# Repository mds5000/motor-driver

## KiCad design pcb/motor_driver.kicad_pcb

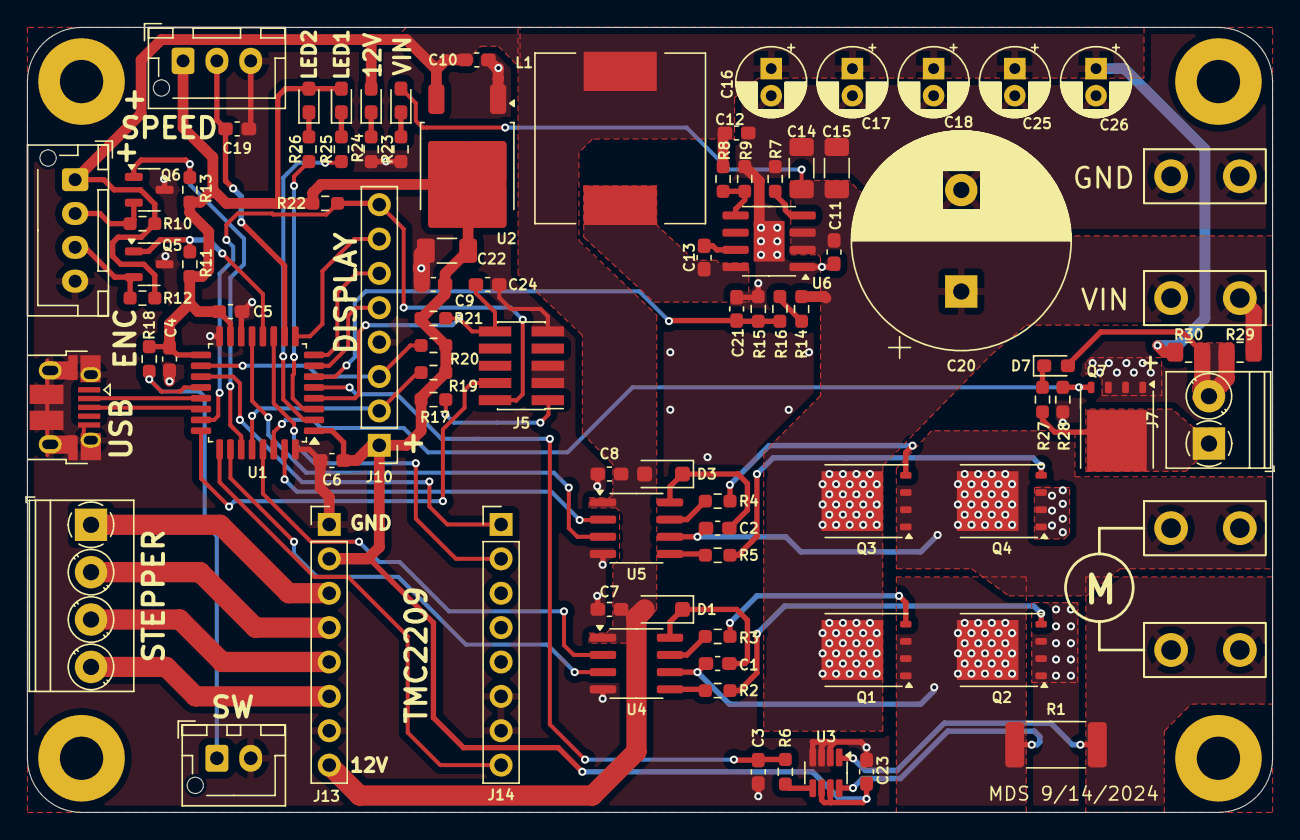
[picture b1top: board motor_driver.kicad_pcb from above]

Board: 2 copper layers, 92.0 x 58.0 mm, 95 parts (0 on the bottom side), 63 nets.

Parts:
C1, C2, C3, C4, C5, C6, C7, C8, C9, C10, C11, C12, C13, C19, C21, C23, C24: 0.1uF; C_0603_1608Metric_Pad1.08x0.95mm_HandSolder
C14, C15: 1uF; C_1206_3216Metric_Pad1.33x1.80mm_HandSolder
C16, C17, C18, C25, C26: 10uF; CP_Radial_D5.0mm_P2.00mm
C20: 470uF; CP_Radial_D16.0mm_P7.50mm
C22: 4.7uF; C_1206_3216Metric_Pad1.33x1.80mm_HandSolder
D1, D3: 1N5819WS; D_SOD-123F
D2, D4, D5, D6, D7: LED; LED_0603_1608Metric_Pad1.05x0.95mm_HandSolder
H1, H2, H3, H4: MountingHole; MountingHole_3.2mm_M3_Pad
J1, J2, J3, J4: 1217861-1; CONN_QuickTab_TE_Conn_1217861-1
J5: Conn_ARM_JTAG_SWD_10; PinHeader_2x05_P1.27mm_Vertical_SMD
J6: Screw_Terminal_01x04; TerminalBlock_Phoenix_PT-1,5-4-3.5-H_1x04_P3.50mm_Horizontal
J7: Screw_Terminal_01x02; TerminalBlock_Phoenix_PT-1,5-2-3.5-H_1x02_P3.50mm_Horizontal
J8: Conn_01x03; JST_XH_B3B-XH-AM_1x03_P2.50mm_Vertical
J9: Conn_01x02; JST_XH_B2B-XH-AM_1x02_P2.50mm_Vertical
J10: Conn_01x08_Pin; PinHeader_1x08_P2.54mm_Vertical
J11: Conn_01x04; JST_XH_B4B-XH-AM_1x04_P2.50mm_Vertical
J12: USB_B_Micro; USB_Micro-B_Amphenol_10103594-0001LF_Horizontal
J13, J14: Conn_01x08_Socket; PinHeader_1x08_P2.54mm_Vertical
L1: 47uH; L_12x12mm_H8mm
Q1, Q2, Q3, Q4: BSC072N08NS5; TDSON-8-1
Q5, Q6: NPN; SOT-23-3
Q7: CSD17303Q5; TDSON-8-1
R1: 20mOhm; R_2512_6332Metric_Pad1.40x3.35mm_HandSolder
R2, R3, R4, R5, R6: 47; R_0603_1608Metric_Pad0.98x0.95mm_HandSolder
R7, R23, R27: 49.9K; R_0603_1608Metric_Pad0.98x0.95mm_HandSolder
R8, R14, R16: 110K; R_0603_1608Metric_Pad0.98x0.95mm_HandSolder
R9, R10, R11, R12, R13, R15, R18, R19, R20, R21, R22, R24, R28: 10K; R_0603_1608Metric_Pad0.98x0.95mm_HandSolder
R17: 220; R_0603_1608Metric_Pad0.98x0.95mm_HandSolder
R25, R26: 1K; R_0603_1608Metric_Pad0.98x0.95mm_HandSolder
R29: 0; R_0805_2012Metric_Pad1.20x1.40mm_HandSolder
R30: DNP; R_0805_2012Metric_Pad1.20x1.40mm_HandSolder
U1: STM32G431KBTx; LQFP-32_7x7mm_P0.8mm
U2: AZ1117-3.3; TO-252-2
U3: INA241A1xDDF; SOT-23-8
U4, U5: LM5109BMA; SOIC-8_3.9x4.9mm_P1.27mm
U6: SOIC-8-1EP_3.9x4.9mm_P1.27mm_EP2.29x3mm

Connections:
+3.3V: C4.1, C5.1, C6.1, C9.1, C22.1, C23.1, D5.2 (A), D6.2 (A), J8.1, J10.1, J13.2, R11.1, R13.1, R17.1, R18.2, R19.2, R20.2, R21.1, R22.1, U1.1 (VDD), U1.15 (VDDA), U1.17 (VDD), U2.2 (VO), U3.6 (V+), U3.7 (REF1)
+12V: C7.1, C8.1, C10.1, C12.1, C16.1, C17.1, C18.1, C25.1, C26.1, D1.2 (A), D3.2 (A), D4.2 (A), J11.1, J13.8, L1.2, R8.2, R10.1, R12.1, R30.2, U2.3 (VI), U4.1 (VDD), U5.1 (VDD)
/BTN_ENT: J5.2 (SWDIO/TMS), J10.8, R22.2, U1.23 (PA13)
/DIR: J14.1, U1.19 (PA9)
/DISP_CLK: J10.3, R20.1, U1.18 (PA8)
/DISP_DAT: J10.2, R19.1, U1.28 (PB5)
/ENABLE: J14.8, U1.25 (PA15)
/ENC_A: J10.5, U1.7 (PA2)
/ENC_B: J10.6, U1.8 (PA3)
/ENC_BTN: J10.7, U1.9 (PA4)
/ISNS: C3.1, R6.2, U1.5 (PA0)
/LED1: R25.1, U1.2 (PF0)
/LED2: R26.1, U1.3 (PF1)
/MTR_A: C1.2, Q1.1 (S), Q1.2 (S), Q1.3 (S), Q2.5 (D), R1.1, U3.8 (+), U4.6 (HS)
/MTR_A_R: J1.1, J1.2, R1.2, U3.1 (-)
/MTR_B: C2.2, J2.1, J2.2, Q3.1 (S), Q3.2 (S), Q3.3 (S), Q4.5 (D), U5.6 (HS)
/NRST: C24.1, J5.10 (~RESET), R21.2, U1.4 (PG10)
/ON_SW: J9.1, R18.1, U1.20 (PA10)
/OVERVOLT: Q7.4 (G), R28.1, U1.30 (PB7)
/PHASE_A: Q6.1 (C), R13.2, U1.27 (PB4)
/PHASE_B: Q5.1 (C), R11.2, U1.12 (PA7)
/SPEED: C19.2, J8.2, U1.10 (PA5)
/STEP: J14.2, U1.11 (PA6)
/SWA_HS: U1.29 (PB6), U4.2 (HI)
/SWA_LS: U1.26 (PB3), U4.3 (LI)
/SWB_HS: U1.31 (PB8), U5.2 (HI)
/SWB_LS: U1.13 (PB0), U5.3 (LI)
/SWCLK: J5.4 (SWCLK/TCK), U1.24 (PA14)
/USB_DN: J12.2 (D-), U1.21 (PA11)
/USB_DP: J12.3 (D+), U1.22 (PA12)
/VIN: C11.1, C14.1, C15.1, C20.1, D2.2 (A), J3.1, J3.2, Q1.5 (D), Q3.5 (D), R14.2, R29.2, U6.2 (EN), U6.3 (VIN)
/VSNS: C21.1, R15.2, R16.1, U1.6 (PA1)
GND: C3.2, C4.2, C5.2, C6.2, C7.2, C8.2, C9.2, C10.2, C11.2, C12.2, C14.2, C15.2, C16.2, C17.2, C18.2, C19.1, C20.2, C21.2, C22.2, C23.2, C24.2, C25.2, C26.2, J4.1, J4.2, J5.3 (GND), J5.5 (GND), J5.9 (GNDDetect), J8.3, J9.2, J10.4, J11.4, J12.5 (GND), J12.6 (Shield), J13.1, J13.7, J14.6, J14.7, Q2.1 (S), Q2.2 (S), Q2.3 (S), Q4.1 (S), Q4.2 (S), Q4.3 (S), Q5.3 (E), Q6.3 (E), Q7.1 (S), Q7.2 (S), Q7.3 (S), R7.1, R9.1, R15.1, R23.1, R24.1, R28.2, U1.14 (VSSA), U1.16 (VSS), U1.32 (VSS), U2.1 (GND), U3.2 (GND), U3.3 (REF2), U3.4 (GND), U4.4 (VSS), U5.4 (VSS), U6.1 (GND), U6.9 (EP)
unnamed: C1.1, D1.1 (K), U4.8 (HB)
unnamed: D2.1 (K), R23.2
unnamed: C2.1, D3.1 (K), U5.8 (HB)
unnamed: D4.1 (K), R24.2
unnamed: D5.1 (K), R25.2
unnamed: D6.1 (K), R26.2
unnamed: D7.2 (A), J7.2, R29.1, R30.1
unnamed: D7.1 (K), R27.2
unnamed: J5.1 (VTref), R17.2
unnamed: J7.1, Q7.5 (D), R27.1
unnamed: J11.2, Q6.2 (B), R10.2
unnamed: J11.3, Q5.2 (B), R12.2
unnamed: J6.1, J13.3
unnamed: J6.2, J13.4
unnamed: J6.3, J13.5
unnamed: J6.4, J13.6
unnamed: Q1.4 (G), R3.2
unnamed: Q2.4 (G), R2.2
unnamed: Q3.4 (G), R4.1
unnamed: Q4.4 (G), R5.1
unnamed: R6.1, U3.5
unnamed: R14.1, R16.2
unnamed: R3.1, U4.7 (HO)
unnamed: R2.1, U4.5 (LO)
unnamed: R4.2, U5.7 (HO)
unnamed: R5.2, U5.5 (LO)
unnamed: C13.1, U6.7 (BOOT)
unnamed: R8.1, R9.2, U6.5 (FB)
unnamed: R7.2, U6.4 (RT/SYNC)
unnamed: C13.2, L1.1, U6.8 (SW)

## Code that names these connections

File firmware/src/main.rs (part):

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    use hal::prelude::*;
    use hal::time::{RateExtU32, ExtU32};
    use stm32g4xx_hal::gpio::{Alternate, AlternateOD, ExtiPin, Input, Output, PullUp, PushPull, AF14, AF15, AF2, AF8};
    use stm32g4xx_hal::gpio::gpioa::{PA11, PA12, PA10, PA7, PA8};
    use stm32g4xx_hal::gpio::gpiob::{PB4, PB5};
    use stm32g4xx_hal::gpio::gpiof::{PF0, PF1};
    use stm32g4xx_hal::rcc::{Config, PllConfig, PllMDiv, PllNMul, PllRDiv};
    use stm32g4xx_hal::pwr::PwrExt;
    use stm32g4xx_hal::usb::{Peripheral, UsbBus};
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
    use defmt::{info, warn};

    type UsbBusType = UsbBus<Peripheral<PA11<Alternate<AF14>>, PA12<Alternate<AF14>>>>;
    systick_monotonic!(Mono, 1_000);

    #[shared]
    struct Shared {
        control: controller::Controller,
        usb_serial: SerialPort<'static, UsbBus<Peripheral<PA11<Alternate<AF14>>, PA12<Alternate<AF14>>>>>,
    }

    const QUEUE_DEPTH: usize = 4;
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    #[local]
    struct Local {
        adc1: adc::Adc1,
        led1: PF0<Output<PushPull>>,
        led2: PF1<Output<PushPull>>,
        motor: motor::Motor,
        usb_dev: UsbDevice<'static, UsbBus<Peripheral<PA11<Alternate<AF14>>, PA12<Alternate<AF14>>>>>,
        msg_tx: Sender<'static, [u8; 32], QUEUE_DEPTH>,
        msg_rx: Receiver<'static, [u8; 32], QUEUE_DEPTH>,
        telem_tx: Sender<'static, [u8; 32], TELEM_DEPTH>,
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
        // Setup Analog to Digital Conversion
        // This must precede PWM setup as the ADC is used to trigger PWM Timer
        let _isns = gpioa.pa0.into_analog();
        let _vsns = gpioa.pa1.into_analog();
        let adc1 = adc::Adc1::new();

        // Motor PWM & GPIO Initialization
        let low_side_a = gpiob.pb3.into_alternate();
        let low_side_b = gpiob.pb0.into_alternate();
        let high_side_a = gpiob.pb6.into_alternate();
        let high_side_b = gpiob.pb8.into_alternate();
        let e_stop = gpioa.pa10.into_alternate();
        let (fault, (pwm_a, pwm_b)) = dp.TIM8.pwm_advanced(
            (high_side_a, high_side_b), &mut rcc)
            .frequency(30.kHz())
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        };

        // End-stops
        // PA5 is wired to two limit switches in series. A open circuit may indicate either
        // positive or negative travel exceeded.
        let mut endstop = gpioa.pa5.into_pull_up_input();
        endstop.make_interrupt_source(&mut syscfg);
        endstop.enable_interrupt(&mut dp.EXTI);
        endstop.trigger_on_edge(&mut dp.EXTI, stm32g4xx_hal::gpio::SignalEdge::Rising);

        // LEDs
        let mut led1 = gpiof.pf0.into_push_pull_output();
        let mut led2 = gpiof.pf1.into_push_pull_output();
        led1.set_low().unwrap();
        led2.set_low().unwrap();

        // GPIO
        let mut fan_en = gpiob.pb7.into_push_pull_output();
        fan_en.set_low().unwrap();

        // USB Virtual Serial Port
        let usb_dm = gpioa.pa11.into_alternate();
        let usb_dp = gpioa.pa12.into_alternate();
        let usb = Peripheral {
            usb: dp.USB,
            pin_dm: usb_dm,
            pin_dp: usb_dp,
        };
        let usb_bus: &'static _ = ctx.local.usb_bus.insert(UsbBus::new(usb));
        let mut usb_serial = SerialPort::new(&usb_bus);
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            .build();

        // Position Encoder
        let enc_a: PB4<Alternate<AF2>> = gpiob.pb4.into_alternate();
        let enc_b: PA7<Alternate<AF2>> = gpioa.pa7.into_alternate();
        let motor_enc = qei::Qei::new(dp.TIM3, enc_a, enc_b);

        let endstop_state = endstop.is_high().unwrap();
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
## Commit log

2024-09-29 Switched to RTIC runtime
2024-10-18 Initial speed control w/ rtic
2024-10-18 complementary outputs
2024-10-20 Torque and Speed control PID tuned.
2024-12-11 Implemented homing routine
2025-06-19 Update motor driver fw
2025-06-19 Added PCB
2025-06-19 Pin HAL version
2025-06-22 Branch for sabertooth dev
